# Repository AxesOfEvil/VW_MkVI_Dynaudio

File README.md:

# Dynaudio Amplifier control for VW MkVI GTI

The MkVI Volkswagen GTI uses CAN bus commands to power on/off as well as
for fade/balance settings

This means that an aftermarket head-unit may not be able to power-on the
amplifier, and thus no sound will be heard.

This project addresses this issue by sending the appropriate power on/off 
commands to the Stock Dynaudio amplifier when the 'Amp Power' wire has
12V on it (alternately, attach the common 'Accessory' wire if the head-unit
has no 'Amp Power' wire)

# How it works
The cirucit uses a self-latching power circuit for low-power operation.
When 12V is detected on the 'Amp Power' wire, the circuit will power up.
The Arduino will then keep the circuit powered even if 'Amp Power' is turned
off.

When the Arduino detects the 'Amp Power' at 12V, it will send the Dynaudio
amplifier the power up signals via the CAN bus, and go to sleep.

When the 'Amp Power' wire drops to 0V, the Arduino will wakeup, send the
power-down sequence to the Dynaudio amplifier, and then turn itself off.
Once off, the only way to power up the Arduino again is to apply 12V to the
'Amp Power' wire.

# About the schematic
An AVR based arduino is used because of its 5V tolerance. Specifically,
either a 'Pro Micro' or 'Pro Mini' Arduino is recommended.  It should not
matter if the Arduino board is a 5V or 3.3V variant (both are capable of being
powered at 5V).

The LDO can be replaced with a DC/DC supply to further reduce current, though
the difference is only ~100mW of power (when active, the circuit consumes
negligible power when the 'Power Amp' wire is inactive)

I prefered to use an Arduino 'Pro Micro' instead of the 'Pro Mini' primarily
because it has a USB interface that could be used in the future to control
additional CAN bus functions.  However, the 'Pro Micro' uses USB programming
which does not play very nicely with the low-power states used by software.
When using a 'Pro Micro' it is recommended, to flash the 'Optiboot' firmware
such that the board can be programmed via Serial1 instead of via USB.

# Building the software
The software uses the following Arduino libraries:

* `Arduino-MCP2515` : https://github.com/autowp/arduino-mcp2515
* `Low Power`

# CAN bus protocol
The Dynaudio amplifier listens on interface 0x6C7 for amplifier commands.
As the commands were snooped from a working head-unit, their individual
function is not fully known.

Power up seems to require a minimum of 5 frames, with the 1st byte being
0x1B or 0x2B.  After power-on, and additional 13 frames are sent to set the
fade/balance/etc settings, but the meaning of these frames is not yet known.

Power-down requires only a single frame (with 1st byte = 0x2b)

# VW Media Can bys data (100kbps)

| Identifier | Data                    | Description |
| -----------| ----------------------- | ----------- |
| 0x5C1      | 06 00 00 60             | vol up (repeats periodically while button is held) |
| 0x5C1      | 07 00 00 60             | vol down (repeats periodically while button is held) |
| 0x5C1      | 03 00 00 60             | left button (repeats periodically while button is held) |
| 0x5C1      | 02 00 00 60             | right button (repeats periodically while button is held) |
| 0x5C1      | 2A 00 00 60             | mic button (repeats periodically while button is held) |
| 0x5C1      | 1A 00 00 60             | phone button (repeats periodically while button is held) |
| 0x5C1      | 29 00 00 60             | return button (repeats periodically while button is held) |
| ---------- | ----------------------- | ----------- |
| 0x6C7      | 80 04 2B 57 00 05 01 xx | Dynaudio amp left/right fade (8-bit signed int. 0x80 = full left, 0x7f = full right |
| 0x6C7      | 80 04 2B 58 00 05 01 xx | Dynaudio amp front/back balance (8-bit signed int. 0x80 = full back, 0x7f = full front |
| 0x6C7      | 2B 50 00                | Dynaudio amp power down |
| 0x6C7      | 1B 42                   | Dynaudio amp ??? (powerup frame 1) |
| 0x6C7      | 1B 43                   | Dynaudio amp ??? (powerup frame 2) |
| 0x6C7      | 1B 41                   | Dynaudio amp ??? (powerup frame 3) |
| 0x6C7      | 2B 50 01                | Dynaudio amp ??? (powerup frame 4) - power up ? |
| 0x6C7      | 2B 53 00                | Dynaudio amp ??? (powerup frame 5) |
| 0x6C7      | 80 07 2B 55 78 00 00 00 | Dynaudio amp ??? (powerup frame 6) - resent periodically |
| 0x6C7      | C0 22 22 00             | Dynaudio amp ??? (powerup frame 7) - resent periodically |
| 0x6C7      | 80 07 2B 51 00 00 04 05 | Dynaudio amp ??? (powerup frame 8) |
| 0x6C7      | C0 0A 08 FF             | Dynaudio amp ??? (powerup frame 9) |
| 0x6C7      | 80 03 1B 52 00 00 0D    | Dynaudio amp ??? (powerup frame 10) |
| 0x6C7      | 80 03 1B 54 00 00 0D    | Dynaudio amp ??? (powerup frame 11) |
| 0x6C7      | 80 03 1B 57 00 00 0D    | Dynaudio amp ??? (powerup frame 12) |
| 0x6C7      | 80 03 1B 58 00 00 0D    | Dynaudio amp ??? (powerup frame 13) |
| 0x6C7      | 80 03 1B 59 00 00 0D    | Dynaudio amp ??? (powerup frame 14) |
| 0x6C7      | 80 03 1B 5A 00 00 0D    | Dynaudio amp ??? (powerup frame 15) |
| 0x6C7      | 80 03 1B 5B 00 00 0D    | Dynaudio amp ??? (powerup frame 16) |
| 0x6C7      | 80 03 1B 5C 00 00 04    | Dynaudio amp ??? (powerup frame 17) |
| 0x6C7      | 80 03 1B 5E 00 00 04    | Dynaudio amp ??? (powerup frame 18) |
| ---------- | ----------------------- | The following data was collected by hugovw1976 (see link below) |
| 0x2C3      | aa                      | aa: bit0 power on |
| 0x635      | aa bb cc                | aa: bit0 lights on |
| 0x466      | aa bb cc dd ee ff gg hh | bb: door-open - bit0: driver, bit1: passenger, bit2: rear-driver, bit3: rear passenger, bit4: hood, bit5: trunk |
| 0x35B      | aa bb cc dd ee ff gg hh | ccbb: RPM*4 (unconfirmed) |
| 0x527      | aa bb cc dd ee ff gg hh | ccbb: Speed (units?) (unconfirmed), ff: (outside temperature(C) +50)/2 |
| 0x621      | aa bb cc dd ee ff gg    | aa: bit 2: wiper state, dd: fuel level (liters) (bit 7 is set to indicate low-fuel when <10l) |
| 0x65D      | aa bb cc dd ee ff gg hh | ddeecc: odometer (unconfirmed) |
| 0x351      | aa bb cc dd ee ff gg hh | aa: bit0: reverse (unconfirmed), cc: bit0: brake (unconfirmed)|
| 0x571      | aa bb cc dd ee ff       | aa: (battery voltage * 10 + 50) / 2 |
| 0x151      | aa bb cc dd             | bb: seat-belt (unconfirmed) |

# Additional Resources
* Using a Raspberry Pi to snoop the CAN bus with a $3 Ebay MCP2515
  * This modification allows running the SPI interface at 3.3V while running
    the CAN interface at 5V: https://forums.raspberrypi.com/viewtopic.php?t=141052
  * Savvy CANbus GUI: https://www.savvycan.com/

* Pinout for VW MkBI head unit
  * https://pinoutguide.com/Car-Stereo-Volkswagen-Porsche/Volkswagen_RCD_310_Head_U_pinout.shtml
  * https://connector.pinoutguide.com/40__16_12_12__pin_Head_Unit_Car_Stereo_Quadlock/

* Interesting articles on CAN bus hacking
  * General overview: https://theksmith.com/software/hack-vehicle-bus-cheap-easy-part-2/
  * Analyzing a VW Gauge cluster using CAN bus hacking (also shows how to use
    the 'savvy' CAN bus analyzer GUI: https://www.youtube.com/watch?v=GOuglqFtmOE&t=23s
  * CANid database for various vendors: https://github.com/iDoka/awesome-automotive-can-id
  * DTB files for CANids for various vendors: https://github.com/commaai/opendbc
  * XDA posting by hugovw1976 with some Golf6 Canids: https://forum.xda-developers.com/t/mtcd-kgl-px5-canbus-problem-with-vw-golf-6.3632690/post-73939457

* Installing Optiboot on Pro Micro
  * NOTE: The official Optiboot github repo supports the Atmega32U4 now.
    https://www.instructables.com/How-to-upload-sketches-to-Pro-MicroLeonardo-via-se/
  * Optiboot home: https://github.com/Optiboot/optiboot/wiki

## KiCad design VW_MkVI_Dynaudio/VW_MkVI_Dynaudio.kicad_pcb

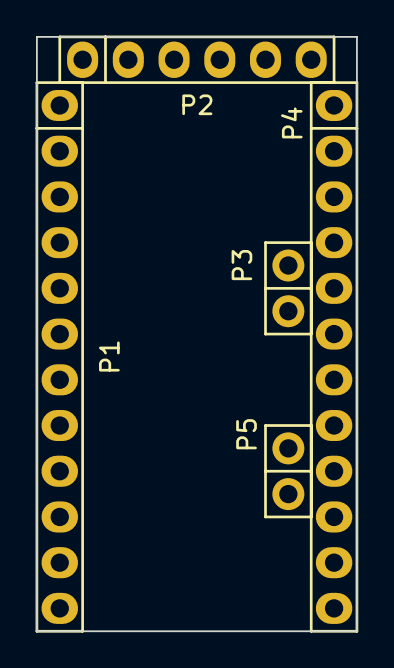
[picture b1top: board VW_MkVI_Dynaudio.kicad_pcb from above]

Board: 2 copper layers, 17.8 x 33.0 mm, 5 parts (0 on the bottom side), 5 nets, no tracks yet.

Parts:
P1: Digital; Socket_Strip_Arduino_1x12
P2: COM; Socket_Strip_Arduino_1x06
P3, P5: ADC; Socket_Strip_Arduino_1x02
P4: Analog; Socket_Strip_Arduino_1x12

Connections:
/0(Rx): P1.2, P2.3
/1(Tx): P1.1, P2.2
/Reset: P1.3, P4.3
GND: P1.4, P2.5, P2.6, P4.2
VCC: P2.4, P4.4

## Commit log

2022-05-22 Initial version
2022-05-22 Add button canid messages
2022-05-22 Add dynaudio amp canid messages
2022-05-22 Add more canid from hugovw1976
